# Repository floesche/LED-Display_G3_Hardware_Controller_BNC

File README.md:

---
title: BNC Breakout
parent: Generation 3
---

## Project content

```
├── gerber_v1.0
├── gerber_v1.1
│   └── old
├── lib
└── mod
```

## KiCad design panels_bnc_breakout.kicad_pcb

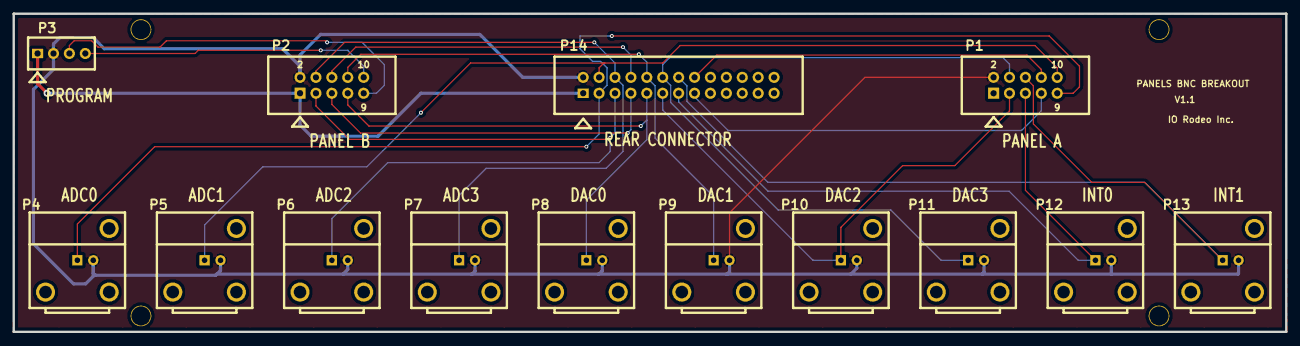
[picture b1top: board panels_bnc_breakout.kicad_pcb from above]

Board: 2 copper layers, 203.2 x 50.8 mm, 18 parts (0 on the bottom side), 18 nets.

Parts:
MOUNT_HOLE: VAL**; MOUNT_HOLE
MOUNT_HOLE#2, MOUNT_HOLE#3, MOUNT_HOLE#4: VAL**; MOUNT_HOLE
P1, P2: CONN_5X2; HEADER_5x2_LARGE
P3: CONN_4; conn_sh_4x1
P4, P5, P6, P7, P8, P9, P10, P11, P12, P13: CONN_2; BNC
P14: CONN_26; conn_sh_26x2

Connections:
/5V: P2.1, P3.1, P14.1
/ADC0: P1.9, P4.1, P14.3
/ADC1: P1.10, P5.1, P14.4
/ADC2: P2.3, P6.1, P14.5
/ADC3: P2.4, P7.1, P14.6
/ADC4: P2.5, P14.7
/ADC5: P2.6, P14.8
/DAC0: P2.7, P8.1, P14.9
/DAC1: P2.8, P9.1, P14.10
/DAC2: P1.3, P10.1, P14.11
/DAC3: P1.4, P11.1, P14.12
/GND: P1.2, P2.2, P3.2, P4.2, P5.2, P6.2, P7.2, P8.2, P9.2, P10.2, P11.2, P12.2, P13.2, P14.2
/INT0: P1.5, P12.1, P14.13
/INT1: P1.6, P13.1, P14.14
/INT2: P1.7, P14.15
/INT3: P1.8, P14.16
/SCL: P2.9, P3.3
/SDA: P2.10, P3.4

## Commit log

2010-12-08 Project creation.
2010-12-08 Added creative commons license.
2010-12-23 Added gerber files for version 1.0 and BOM.
2011-01-24 Fixed bug in pcb schematic DAC1 and DAC3 where swapped similarly, DAC2 and DAC0 where swapped. Created new ps and pdf versions of the schmatic. Created new set of gerber and drill fills. Version numb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
2011-02-03 Re-made v1.1 gerber files.
2011-09-09 Added rear connector pinout.
2015-08-14 Added new version of gerber files + .zip archive for ordering.
2015-08-14 Added drill file.
2015-08-14 Fixed issue with zones.
2020-08-06 getting ready for panel page
2021-11-09 update license, fix text
2021-11-09 update license format
2021-11-09 improve documentation
2021-11-09 add back breakout
2021-11-09 fix links
2021-11-12 reorder menu
2021-11-12 cleanup bnc
2021-11-12 repair schema
2021-11-12 update production files
2021-11-12 fix links:
2021-11-19 fix typo, optimize images
2021-11-19 optimize images
2021-11-30 consistent documentation
2022-11-08 update link
2022-11-08 fix link
